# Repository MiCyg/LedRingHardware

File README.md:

# LedRingHardware

## Description

LedRingHardware is a simple PCB devBoard based on the RP2040 microcontroller, featuring 8 programmable LEDs and battery supply. This project was created to explore the capabilities of MicroPython and CircuitPython.

## Visualization
<p align="center">
  
&nbsp; &nbsp; &nbsp; &nbsp;
  
</p>

## Installation

- Enter to **BOOTSEL** mode connect **boot** testpoints placed close to **U3** chip.
- Download CircuitPython firmware for rp2040. There is avaliable [here](https://downloads.circuitpython.org/bin/raspberry_pi_pico/pl/adafruit-circuitpython-raspberry_pi_pico-pl-9.1.1.uf2) or for latest version go to [CircuitPython](https://circuitpython.org/) site.
- Copy `.uf2` firmware to device

## Example code

```python

import board
import time
import neopixel

LED_NUMBER = 8
BUTTON_PIN = board.GP22
LED_PIN = board.GP13

COLOR = (10,0,15)
disp_pix = neopixel.NeoPixel(LED_PIN, LED_NUMBER, auto_write=False)

while True:
	for i in range(LED_NUMBER):
		disp_pix[i] = COLOR
		disp_pix.show()
		time.sleep(0.1)
		
	for i in range(LED_NUMBER):
		disp_pix[i] = (0,0,0)
		disp_pix.show()
		time.sleep(0.1)
```

Expected results will be that:

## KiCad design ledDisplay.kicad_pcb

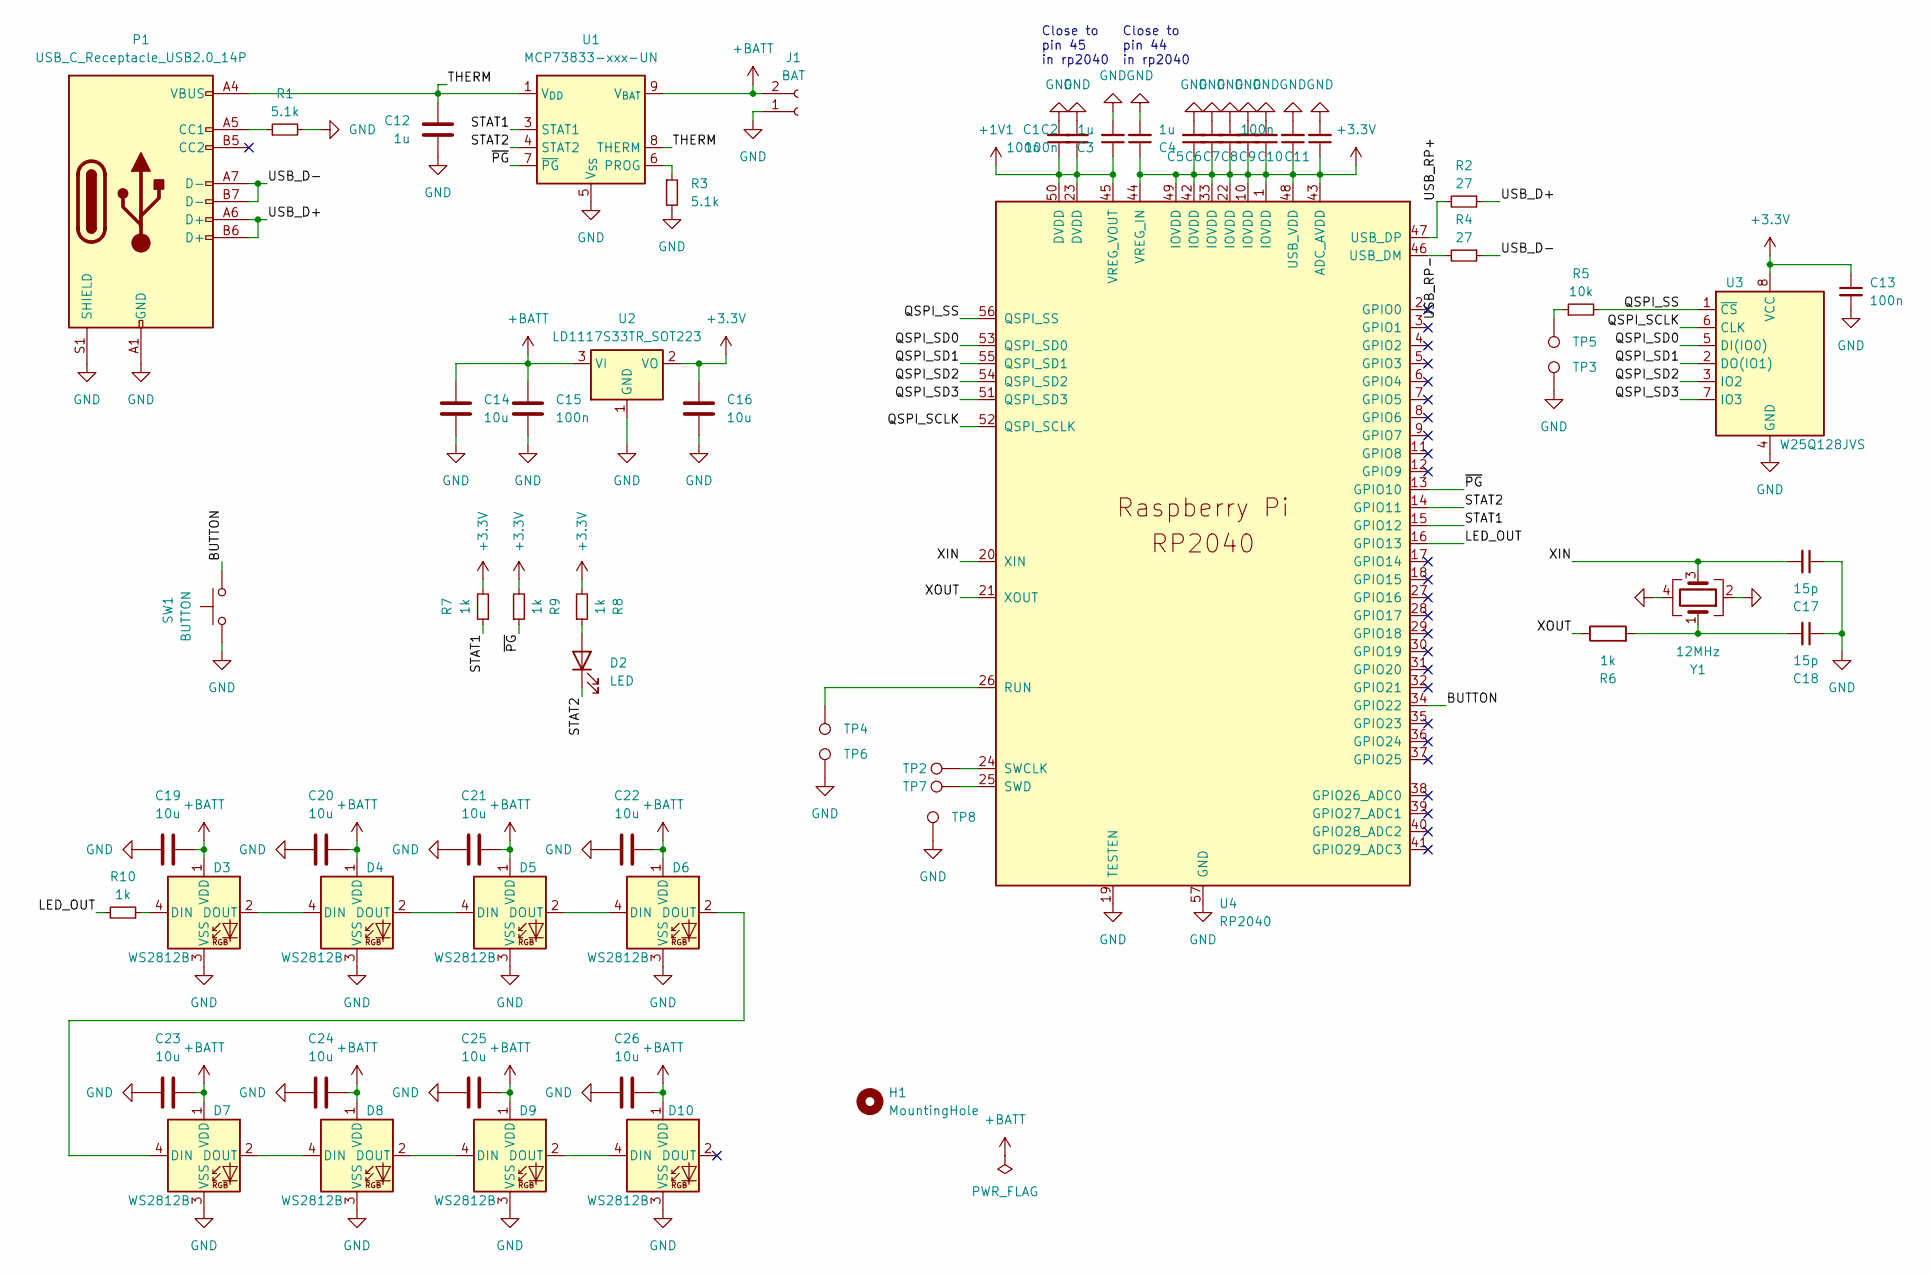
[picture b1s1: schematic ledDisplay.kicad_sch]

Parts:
C1, C2, C5, C6, C7, C8, C9, C10, C11, C13: 100n; C_0603_1608Metric_Pad1.08x0.95mm_HandSolder
C3, C4: 1u; C_0603_1608Metric_Pad1.08x0.95mm_HandSolder
C12: 1u; C_0805_2012Metric_Pad1.18x1.45mm_HandSolder
C14, C16, C19, C20, C21, C22, C23, C24, C25, C26: 10u; C_0805_2012Metric_Pad1.18x1.45mm_HandSolder
C15: 100n; C_0805_2012Metric_Pad1.18x1.45mm_HandSolder
C17, C18: 15p; C_0603_1608Metric_Pad1.08x0.95mm_HandSolder
D2: LED; LED_0603_1608Metric_Pad1.05x0.95mm_HandSolder
D3, D4, D5, D6, D7, D8, D9, D10: WS2812B; LED_WS2812B_PLCC4_5.0x5.0mm_P3.2mm
H1: MountingHole; MountingHole_3.2mm_M3
J1: BAT; PinSocket_1x02_P2.54mm_Horizontal
P1: USB_C_Receptacle_USB2.0_14P; USB_C_Receptacle_G-Switch_GT-USB-7010ASV
R1, R3: 5.1k; R_0603_1608Metric_Pad0.98x0.95mm_HandSolder
R2, R4: 27; R_0603_1608Metric_Pad0.98x0.95mm_HandSolder
R5: 10k; R_0603_1608Metric_Pad0.98x0.95mm_HandSolder
R6, R7, R8, R9, R10: 1k; R_0603_1608Metric_Pad0.98x0.95mm_HandSolder
SW1: BUTTON; SW_Push_1P1T_NO_6x6mm_H9.5mm
TP2, TP3, TP4, TP5, TP6, TP7, TP8: TestPoint; TestPoint_Pad_D1.5mm
U1: MCP73833-xxx-UN; MSOP-10_3x3mm_P0.5mm
U2: LD1117S33TR_SOT223; SOT-223-3_TabPin2
U3: W25Q128JVS; SOIC-8_5.23x5.23mm_P1.27mm
U4: RP2040; RP2040-QFN-56
Y1: 12MHz; Crystal_SMD_SeikoEpson_TSX3225-4Pin_3.2x2.5mm_HandSoldering

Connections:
+1V1: C1.1, C2.1, C3.1, U4.23 (DVDD), U4.45 (VREG_VOUT), U4.50 (DVDD)
+3.3V: C4.1, C5.1, C6.1, C7.1, C8.1, C9.1, C10.1, C11.1, C13.1, C16.1, R7.2, R8.2, R9.2, U2.2 (VO), U3.8 (VCC), U4.1 (IOVDD), U4.10 (IOVDD), U4.22 (IOVDD), U4.33 (IOVDD), U4.42 (IOVDD), U4.43 (ADC_AVDD), U4.44 (VREG_IN), U4.48 (USB_VDD), U4.49 (IOVDD)
+BATT: C14.1, C15.1, C19.1, C20.1, C21.1, C22.1, C23.1, C24.1, C25.1, C26.1, D3.1 (VDD), D4.1 (VDD), D5.1 (VDD), D6.1 (VDD), D7.1 (VDD), D8.1 (VDD), D9.1 (VDD), D10.1 (VDD), J1.2, U1.9 (V_{BAT}), U1.10 (V_{BAT}), U2.3 (VI)
/BUTTON: SW1.1, U4.34 (GPIO22)
/LED_OUT: R10.2, U4.16 (GPIO13)
/QSPI_SCLK: U3.6 (CLK), U4.52 (QSPI_SCLK)
/QSPI_SD0: U3.5 (DI(IO0)), U4.53 (QSPI_SD0)
/QSPI_SD1: U3.2 (DO(IO1)), U4.55 (QSPI_SD1)
/QSPI_SD2: U3.3 (IO2), U4.54 (QSPI_SD2)
/QSPI_SD3: U3.7 (IO3), U4.51 (QSPI_SD3)
/QSPI_SS: R5.2, U3.1 (~CS), U4.56 (QSPI_SS)
/STAT1: R7.1, U1.3 (STAT1), U4.15 (GPIO12)
/STAT2: D2.1 (K), U1.4 (STAT2), U4.14 (GPIO11)
/THERM: C12.1, P1.A4 (VBUS), P1.A9 (VBUS), P1.B4 (VBUS), P1.B9 (VBUS), U1.1 (V_{DD}), U1.2 (V_{DD}), U1.8 (THERM)
/USB_D+: P1.A6 (D+), P1.B6 (D+), R2.1
/USB_D-: P1.A7 (D-), P1.B7 (D-), R4.1
/USB_RP+: R2.2, U4.47 (USB_DP)
/USB_RP-: R4.2, U4.46 (USB_DM)
/XIN: C17.2, U4.20 (XIN), Y1.3
/XOUT: R6.1, U4.21 (XOUT)
/~PG: R9.1, U1.7 (~PG), U4.13 (GPIO10)
GND: C1.2, C2.2, C3.2, C4.2, C5.2, C6.2, C7.2, C8.2, C9.2, C10.2, C11.2, C12.2, C13.2, C14.2, C15.2, C16.2, C17.1, C18.1, C19.2, C20.2, C21.2, C22.2, C23.2, C24.2, C25.2, C26.2, D3.3 (VSS), D4.3 (VSS), D5.3 (VSS), D6.3 (VSS), D7.3 (VSS), D8.3 (VSS), D9.3 (VSS), D10.3 (VSS), J1.1, P1.A1 (GND), P1.A12 (GND), P1.B1 (GND), P1.B12 (GND), P1.S1 (SHIELD), R1.2, R3.2, SW1.2, TP3.1, TP6.1, TP8.1, U1.5 (V_{SS}), U2.1 (GND), U3.4 (GND), U4.19 (TESTEN), U4.57 (GND), Y1.2, Y1.4
unnamed: C18.2, R6.2, Y1.1
unnamed: D2.2 (A), R8.1
unnamed: D3.4 (DIN), R10.1
unnamed: D3.2 (DOUT), D4.4 (DIN)
unnamed: D4.2 (DOUT), D5.4 (DIN)
unnamed: D5.2 (DOUT), D6.4 (DIN)
unnamed: D6.2 (DOUT), D7.4 (DIN)
unnamed: D7.2 (DOUT), D8.4 (DIN)
unnamed: D8.2 (DOUT), D9.4 (DIN)
unnamed: D9.2 (DOUT), D10.4 (DIN)
unnamed: P1.A5 (CC1), R1.1
unnamed: R5.1, TP5.1
unnamed: R3.1, U1.6 (PROG)
unnamed: TP4.1, U4.26 (RUN)
unnamed: TP2.1, U4.24 (SWCLK)
unnamed: TP7.1, U4.25 (SWD)

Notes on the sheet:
Close to pin 45 in rp2040
Close to pin 44 in rp2040

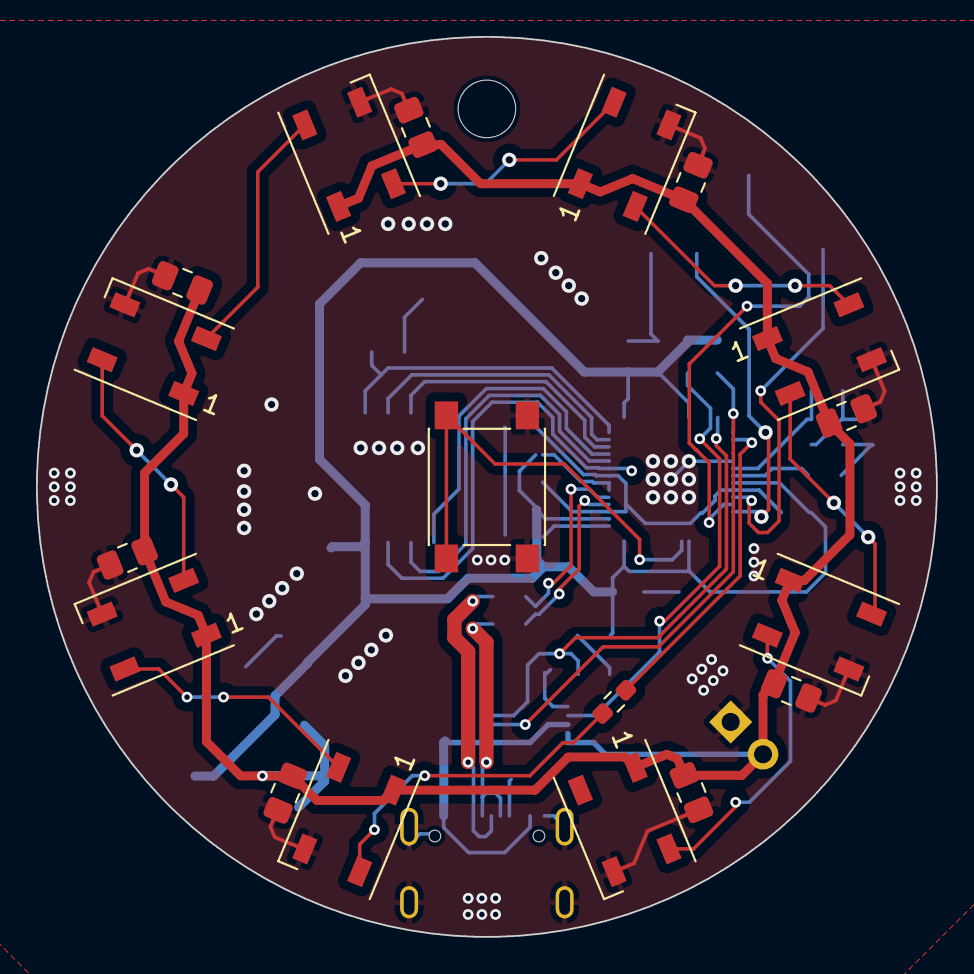
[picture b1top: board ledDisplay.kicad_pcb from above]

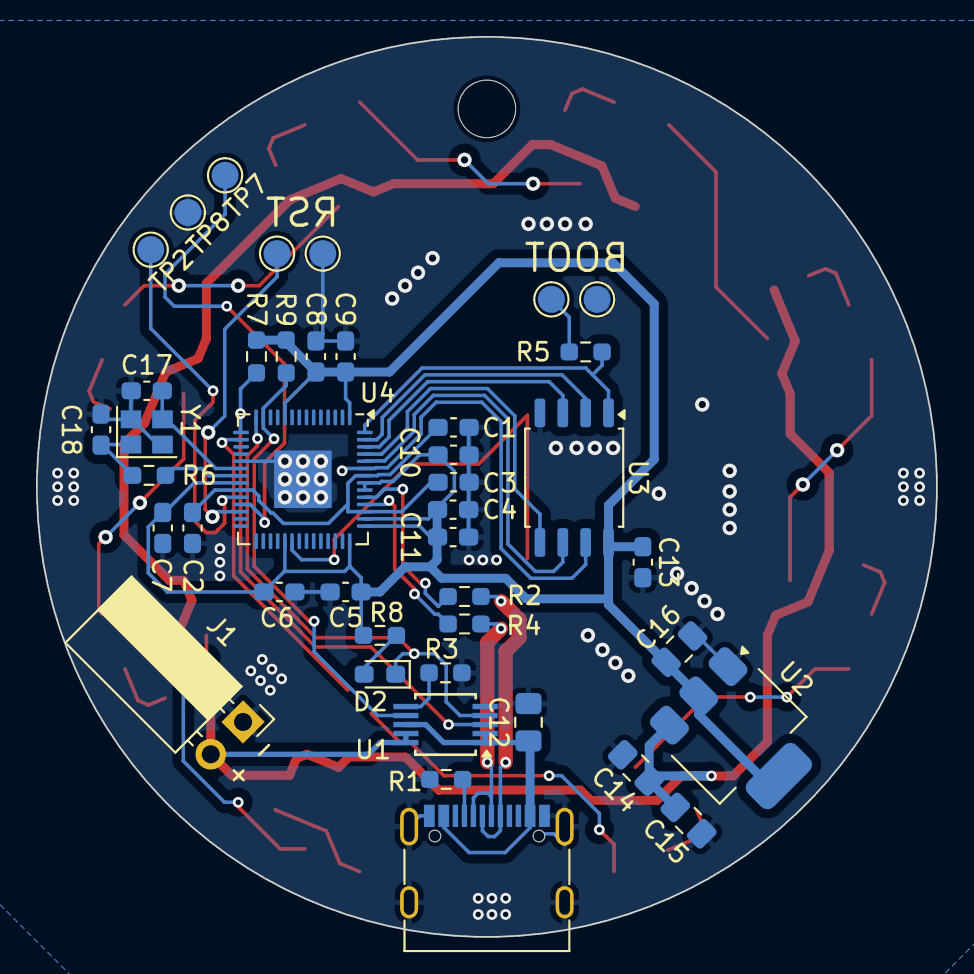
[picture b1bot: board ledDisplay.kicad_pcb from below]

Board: 2 copper layers, 50.0 x 50.0 mm, 61 parts (42 on the bottom side), 38 nets.

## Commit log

2024-06-20 add step file
2024-07-25 change PCB descriptions
2024-07-25 update pcb
